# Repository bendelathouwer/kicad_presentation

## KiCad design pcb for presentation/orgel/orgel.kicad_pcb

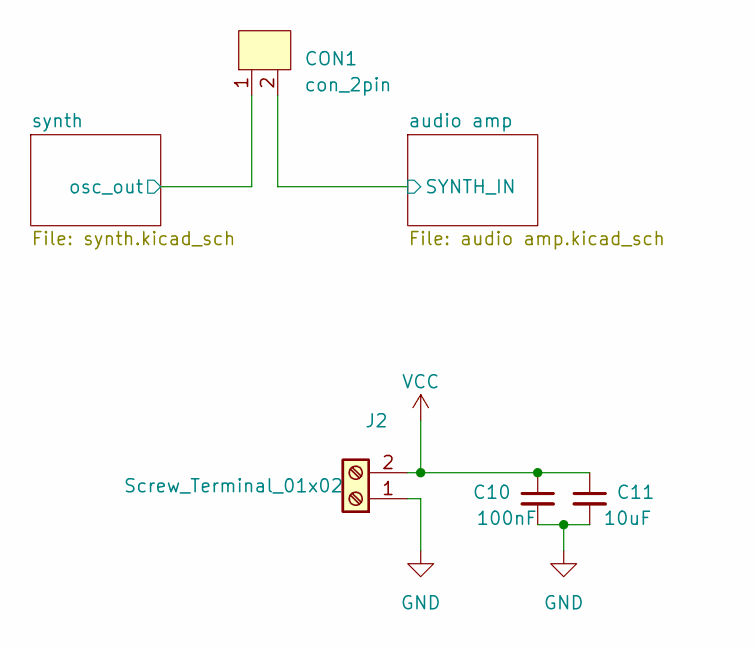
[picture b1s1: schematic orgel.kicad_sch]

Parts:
C10: 100nF; 0603
C11: 10uF; 0603
CON1: con_2pin; 2 pin header
J2: Screw_Terminal_01x02; 2pin_screw

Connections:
/audio amp/SYNTH_IN: CON1.2; also elsewhere on the board
/synth/osc_out: CON1.1; also elsewhere on the board
GND: C10.2, C11.2, J2.1; also elsewhere on the board
VCC: C10.1, C11.1, J2.2; also elsewhere on the board

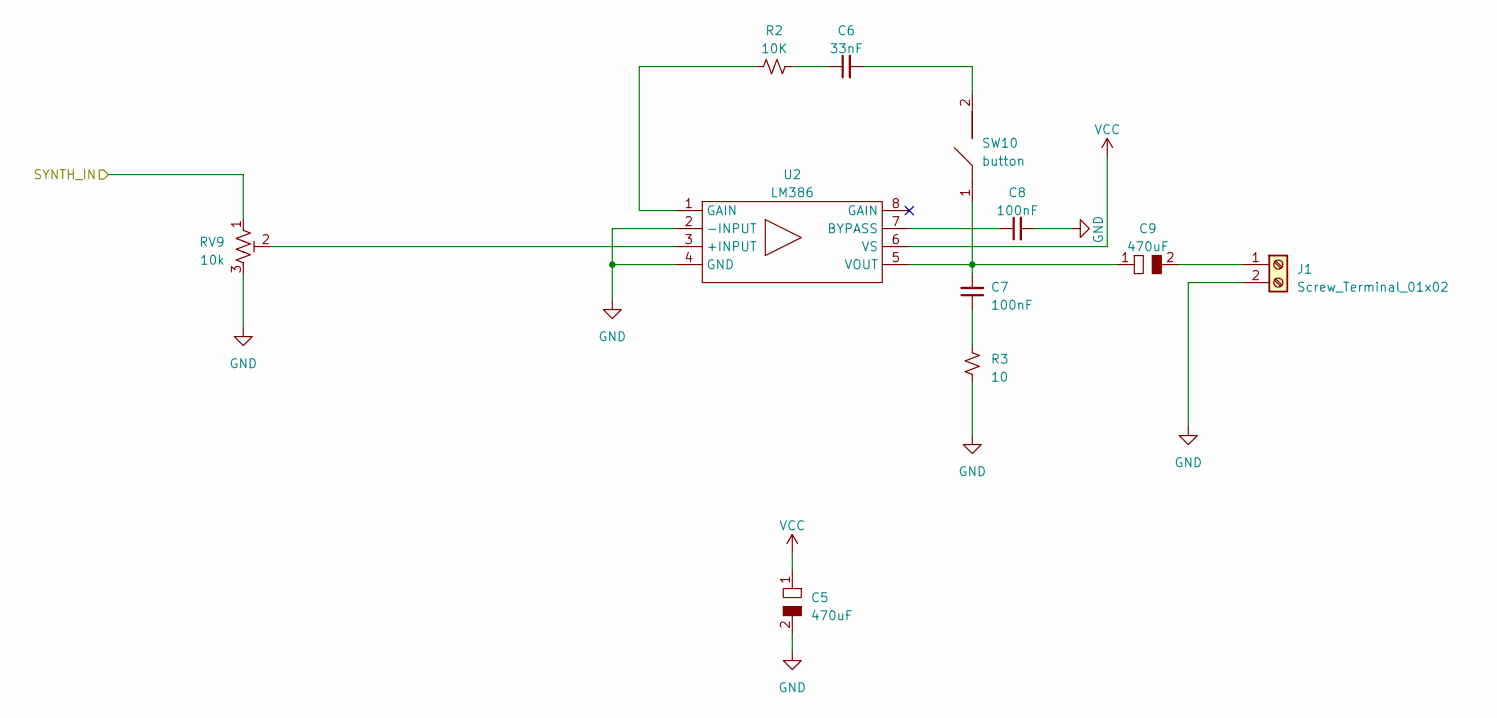
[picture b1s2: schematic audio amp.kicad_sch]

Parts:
C5, C9: 470uF; CAPAE1030X1050D1200L350X90N
C6: 33nF; 0603
C7, C8: 100nF; 0603
J1: Screw_Terminal_01x02; 2pin_screw_vast
R2: 10K; 0603RL
R3: 10; 0603RL
RV9: 10k; BOURNS_3214X-1-104E
SW10: button; SOFNG_TS-1187-1526
U2: LM386; lm386

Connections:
/audio amp/SYNTH_IN: RV9.1; also elsewhere on the board
GND: C5.2, C8.2, J1.2, R3.2, RV9.3, U2.2 (-INPUT), U2.4 (GND); also elsewhere on the board
unnamed: C6.1, R2.1
unnamed: C6.2, SW10.2
unnamed: C7.1, R3.1
unnamed: C7.2, C9.1, SW10.1, U2.5 (VOUT)
unnamed: C8.1, U2.7 (BYPASS)
unnamed: C9.2, J1.1
unnamed: R2.2, U2.1 (GAIN)
unnamed: RV9.2, U2.3 (+INPUT)
VCC: C5.1, U2.6 (VS); also elsewhere on the board

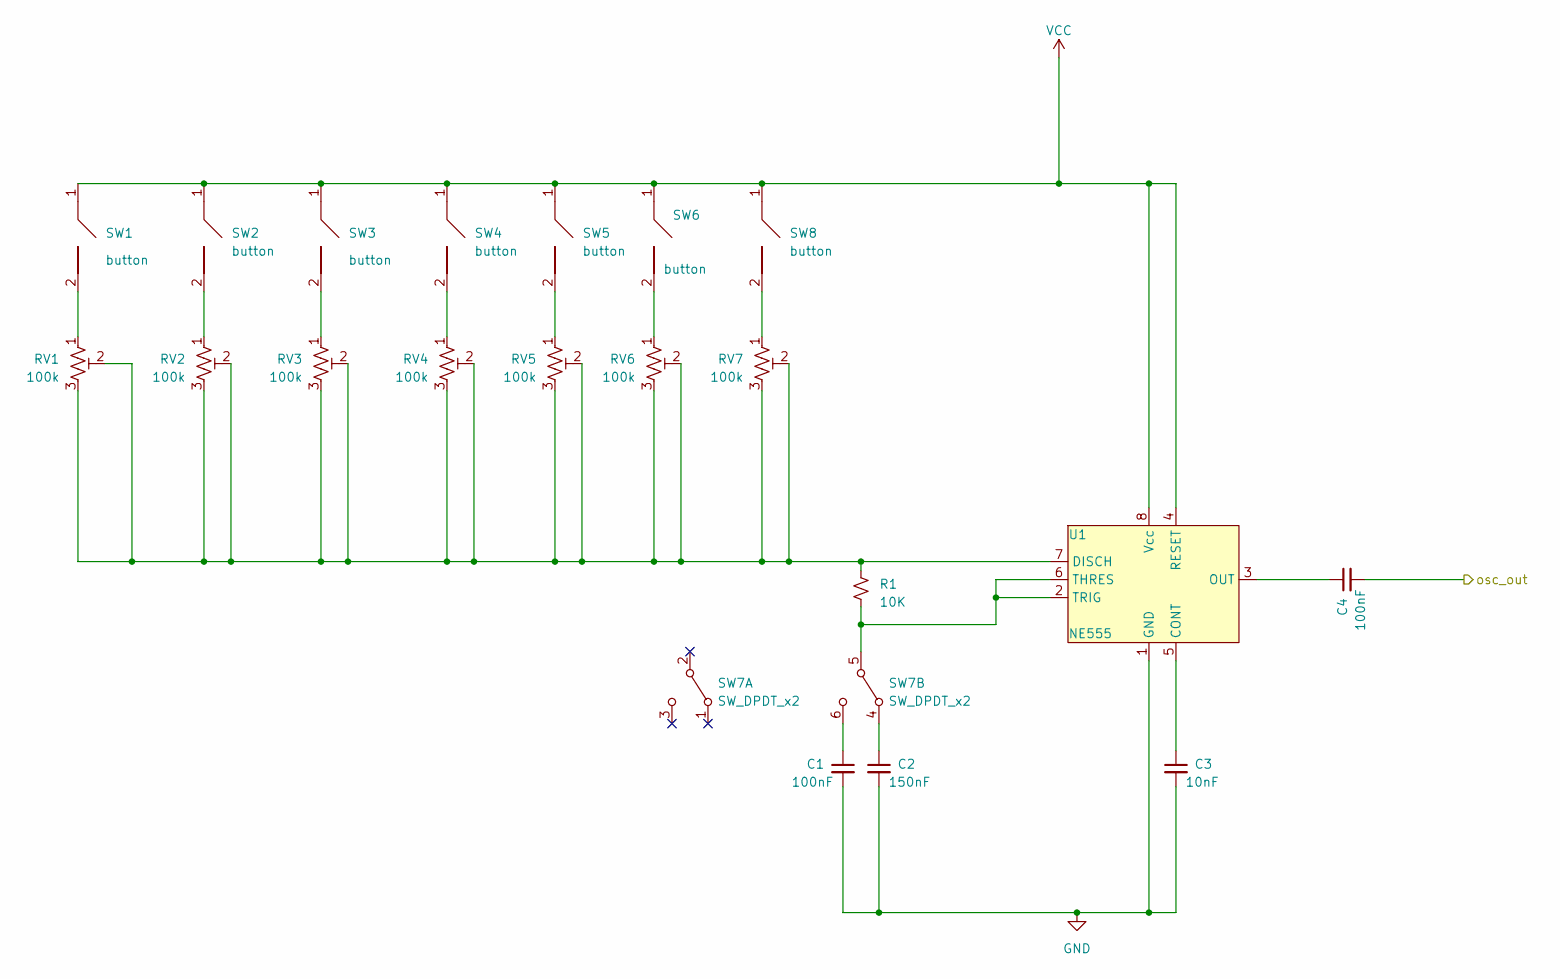
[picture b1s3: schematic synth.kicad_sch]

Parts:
C1, C4: 100nF; 0603
C2: 150nF; 0603
C3: 10nF; 0603
R1: 10K; 0603RL
RV1, RV2, RV3, RV4, RV5, RV6, RV7: 100k; BOURNS_3214X-1-104E
SW1, SW2, SW3, SW4, SW5, SW6, SW8: button; SOFNG_TS-1187-1526
SW7: SW_DPDT_x2; CK_JS202011SCQN
U1: NE555; ne55smd

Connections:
/synth/osc_out: C4.2; also elsewhere on the board
GND: C1.2, C2.2, C3.2, U1.1 (GND); also elsewhere on the board
unnamed: C1.1, SW7.6 (C)
unnamed: C2.1, SW7.4 (A)
unnamed: C3.1, U1.5 (CONT)
unnamed: C4.1, U1.3 (OUT)
unnamed: R1.1, RV1.2, RV1.3, RV2.2, RV2.3, RV3.2, RV3.3, RV4.2, RV4.3, RV5.2, RV5.3, RV6.2, RV6.3, RV7.2, RV7.3, U1.7 (DISCH)
unnamed: R1.2, SW7.5 (B), U1.2 (TRIG), U1.6 (THRES)
unnamed: RV1.1, SW1.2
unnamed: RV2.1, SW2.2
unnamed: RV3.1, SW3.2
unnamed: RV4.1, SW4.2
unnamed: RV5.1, SW5.2
unnamed: RV6.1, SW6.2
unnamed: RV7.1, SW8.2
VCC: SW1.1, SW2.1, SW3.1, SW4.1, SW5.1, SW6.1, SW8.1, U1.4 (RESET), U1.8 (Vcc); also elsewhere on the board

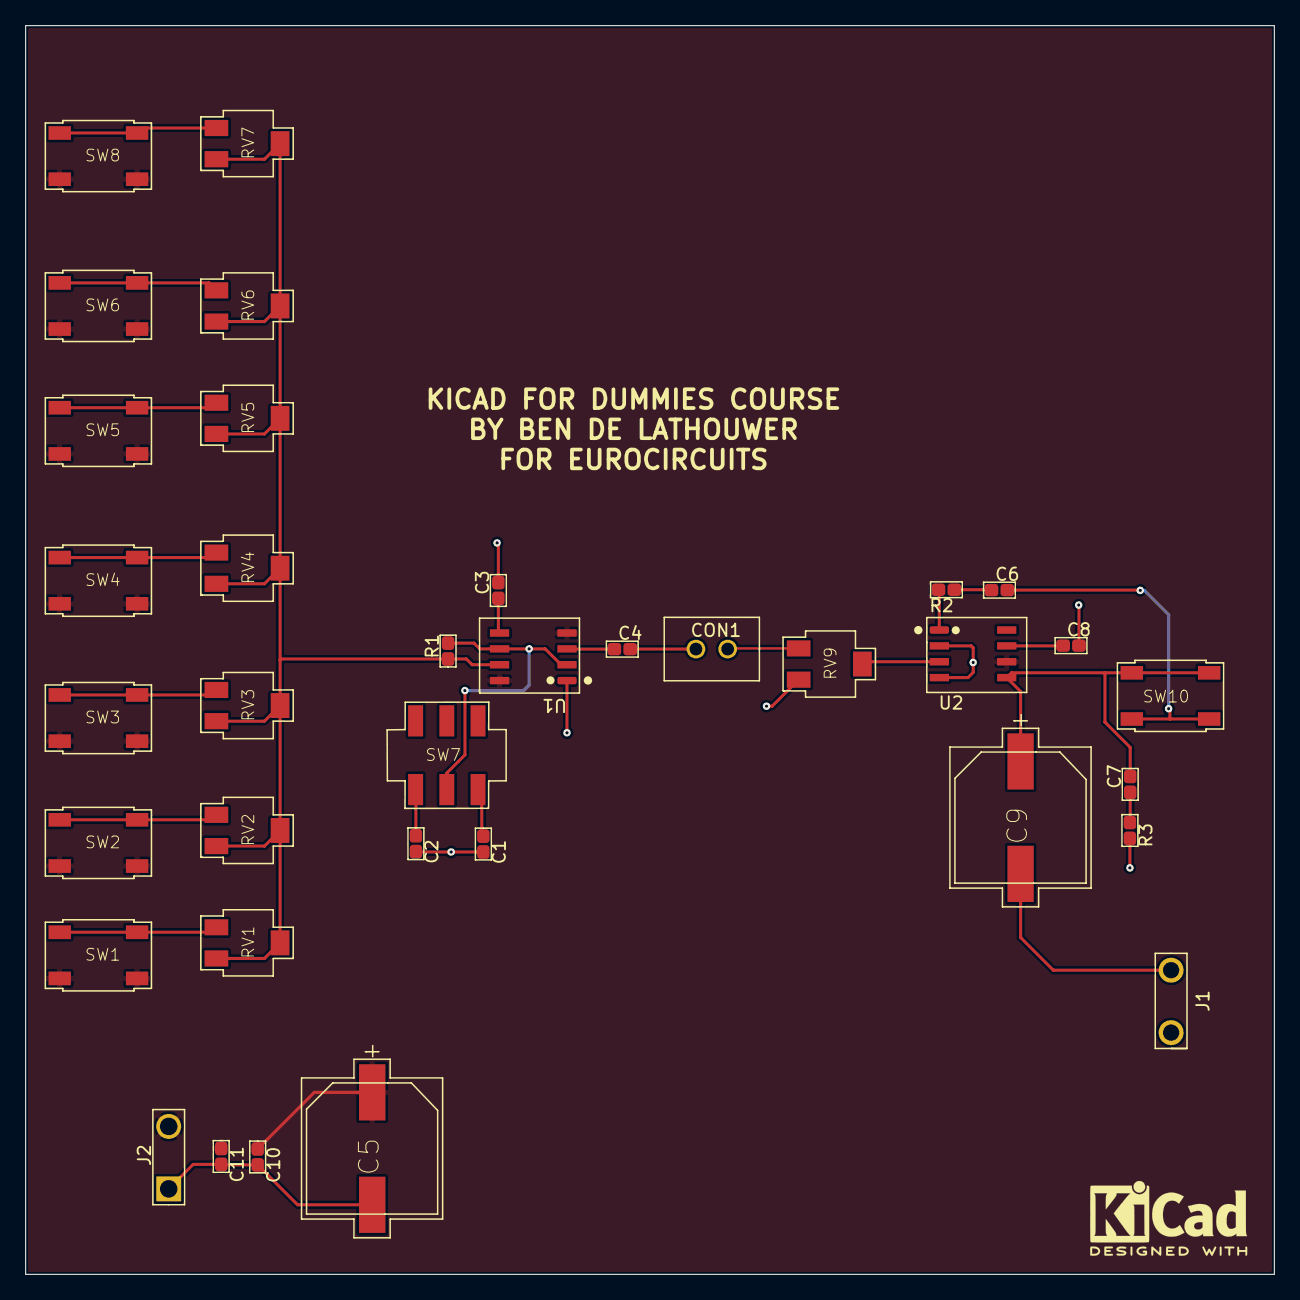
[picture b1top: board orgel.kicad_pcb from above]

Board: 2 copper layers, 100.0 x 100.0 mm, 36 parts (0 on the bottom side), 25 nets.

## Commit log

2021-05-03 les
    oefening voor de les klaar
2021-05-18 tr
    tr
2021-06-22 Create Pcb design for dummies.pptx
    juiste presentatie toegevoegd
